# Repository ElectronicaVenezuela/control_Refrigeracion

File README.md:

# Módulo Control De Refrigeracion Comercial

Tesis para obtar al titulo de ingeniero de la Universidad Nacional Experimental del Táchira (UNET).

## Descripcion

Es un control de refrigeracion comercial con control de ciclos y deshielo, asi como tambien alertas contra posibles anomalias en el sistema de refrigeracion.

## Uso:

 - El hartware fue esta siendo desarrollado en [kicad version Nocturna](http://kicad-pcb.org/download/ubuntu/) para Ubuntu.

 - Las librerias usadas de componentes estan en: 
    -[Symbols](https://github.com/picli3/kicad-symbols.git)
    -[FootPrints](https://github.com/picli3/kicad-footprints.git)
    -[Packages3D](https://github.com/picli3/kicad-packages3D.git)
Se deben clonar y asociarse con el proyecto.

## Autor:

Maykol Rey Maykolrey@gmail.com

## Tutor:

Dr. Cesar contreras.

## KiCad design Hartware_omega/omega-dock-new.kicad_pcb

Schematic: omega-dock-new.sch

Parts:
BT1: 3V; BatteryHolder_Keystone_3000_1x12mm
C1: 22uF; CP_Elec_5x5.3
D1, D2, D3, D4, D6, D7: LED; LED_0603_1608Metric_Castellated
D5: Bridge; MBS -1
J1: SI; HE_XDF1B_1x03_P2.50mm_Horizontal
J2: Termistor; JST_XH_S04B-XH-A-1_1x04_P2.50mm_Horizontal
R1, R2, R3: 100; R_0805_2012Metric_Pad1.15x1.50mm_HandSolder
R4, R5: 2.2K; R_0805_2012Metric_Pad1.15x1.50mm_HandSolder
R6, R7: 10K; R_0805_2012Metric_Pad1.15x1.50mm_HandSolder
R8, R22, R24: 100; R_0805_2012Metric_Pad1.29x1.40mm_HandSolder
R19, R20: 604K; R_0805_2012Metric_Pad1.29x1.40mm_HandSolder
R21: 10k; R_0805_2012Metric_Pad1.29x1.40mm_HandSolder
R23: 10K; R_0805_2012Metric_Pad1.29x1.40mm_HandSolder
SW1: RST; Panasonic_EVQPUL_EVQPUC
U2: OMEGA_2
U11: TLA2024IRUGT; PQFP-N10
U12: DS1307Z+; SOIC-8_3.9x4.9mm_P1.27mm
Y1: 32.768KHZ; Crystal_AT310_D3.0mm_L10.0mm_Horizontal

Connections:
+3V3: R4.1, R5.1, R6.1, R7.1, SW1.1, U2.31, U11.8; also elsewhere on the board
+5V: J1.1, U12.8; also elsewhere on the board
+BATT: BT1.1, U12.3
/GPIO: R24.1, U2.19; also elsewhere on the board
/I_TEST: J1.2, U11.7
/OutTriac/Compresor: D3.2, U2.5; also elsewhere on the board
/OutTriac/Resistencia: D1.2, U2.7; also elsewhere on the board
/OutTriac/Ventilador: D2.2, U2.6; also elsewhere on the board
/SCL: R4.2, U2.18, U11.10, U12.6
/SDA: R5.2, U2.17, U11.9, U12.5
/V_TEST: C1.1, R20.2, R21.1, U11.6; also elsewhere on the board
/error: R22.1, U2.2
/red: R8.1, U2.20
GND: BT1.2, C1.2, D4.1, D5.4, D6.1, D7.1, J1.3, J2.2, J2.4, R1.2, R2.2, R3.2, R21.2, R23.2, U2.1, U2.32, U11.1, U11.3, U12.4; also elsewhere on the board
Nac: D5.2; also elsewhere on the board
unnamed: D1.1, R1.1
unnamed: D2.1, R2.1
unnamed: D3.1, R3.1
unnamed: D4.2, R8.2
unnamed: D5.3, R19.1
unnamed: D6.2, R22.2
unnamed: D7.2, R24.2
unnamed: J2.1, R7.2, U11.4
unnamed: J2.3, R6.2, U11.5
unnamed: R19.2, R20.1
unnamed: R23.1, SW1.2, U2.26
unnamed: U12.1, Y1.1
unnamed: U12.2, Y1.2
VacF: D5.1; also elsewhere on the board

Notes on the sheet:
Omega dock\ new
August 7, 2017
1.0
https://github.com/5N44P/omega-dock-new
address->0x48

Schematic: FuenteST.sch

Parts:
C5, C6: 4,7uF; CP_Radial_D8.0mm_P3.50mm
C7: 10uF; CP_Elec_4x5.3
C8: 1nF; C_0805_2012Metric_Pad1.15x1.50mm_HandSolder
C9: 100uF; CP_Elec_4x5.3
C10: 270uF; CP_Elec_6.3x7.7
C11: 68uF; CP_Elec_6.3x7.7
C12: 100nF; C_1206_3216Metric_Pad1.24x1.80mm_HandSolder
F1: 1A; FC-211-22_M
L2: SDR0503-472JL; SDR0503-XXX
L3: 74479776247; L_0805_2012Metric_Pad1.15x1.50mm_HandSolder
RV1: B72214S0351K101; C_Disc_D4.3mm_W1.9mm_P5.00mm
U3: AP111733; SOT-223
U4: PBO-3-S5

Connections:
+3V3: C9.1, U3.2 (VO), U3.4 (VO); also elsewhere on the board
+5V: C7.1, C11.1, C12.1, L3.2, U3.3 (VI); also elsewhere on the board
/FuenteST/VO: C10.1, L3.1, U4.12
GND: C7.2, C8.2, C9.2, C10.2, C11.2, C12.2, U3.1 (GND), U4.10; also elsewhere on the board
Nac: RV1.2, U4.1; also elsewhere on the board
unnamed: C5.1, C6.1, U4.5
unnamed: C5.2, C6.2, C8.1, U4.7
unnamed: L2.2, U4.3
Vac: F1.2; also elsewhere on the board
VacF: F1.1, L2.1, RV1.1; also elsewhere on the board

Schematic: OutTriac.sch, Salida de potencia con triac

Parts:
C13, C14, C15: 1nF; C_Rect_L13.0mm_W4.0mm_P10.00mm_FKS3_FKP3_MKS4
P1: POWER I/O; WE-3221 - 3.50MM
R10, R11, R12, R13, R14, R15: 330; R_0805_2012Metric_Pad1.15x1.50mm_HandSolder
R16, R18: 33; R_Axial_DIN0207_L6.3mm_D2.5mm_P10.16mm_Horizontal
R17: 100; R_Axial_DIN0207_L6.3mm_D2.5mm_P10.16mm_Horizontal
U5, U6, U7: MOC3063S-TA1; MOC306X
U8, U9, U10: Z0103MN 5AA4; SOT-223-Z01

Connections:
/OutTriac/Compresor: U7.1; also elsewhere on the board
/OutTriac/Resistencia: U6.1; also elsewhere on the board
/OutTriac/Ventilador: U5.1; also elsewhere on the board
CO: P1.4, R15.1, R18.1, U10.2
GND: R10.2, R11.2, R12.2; also elsewhere on the board
Nac: C13.2, C14.2, C15.2, P1.1, U8.1, U9.1, U10.1; also elsewhere on the board
unnamed: C13.1, R16.2
unnamed: C14.1, R17.2
unnamed: C15.1, R18.2
unnamed: R10.1, U5.2
unnamed: R11.1, U6.2
unnamed: R12.1, U7.2
unnamed: R13.2, U5.6
unnamed: R14.2, U6.6
unnamed: R15.2, U7.6
unnamed: U5.4, U8.3
unnamed: U6.4, U9.3
unnamed: U7.4, U10.3
RE: P1.3, R14.1, R17.1, U9.2
VE: P1.2, R13.1, R16.1, U8.2
Vac: P1.5; also elsewhere on the board

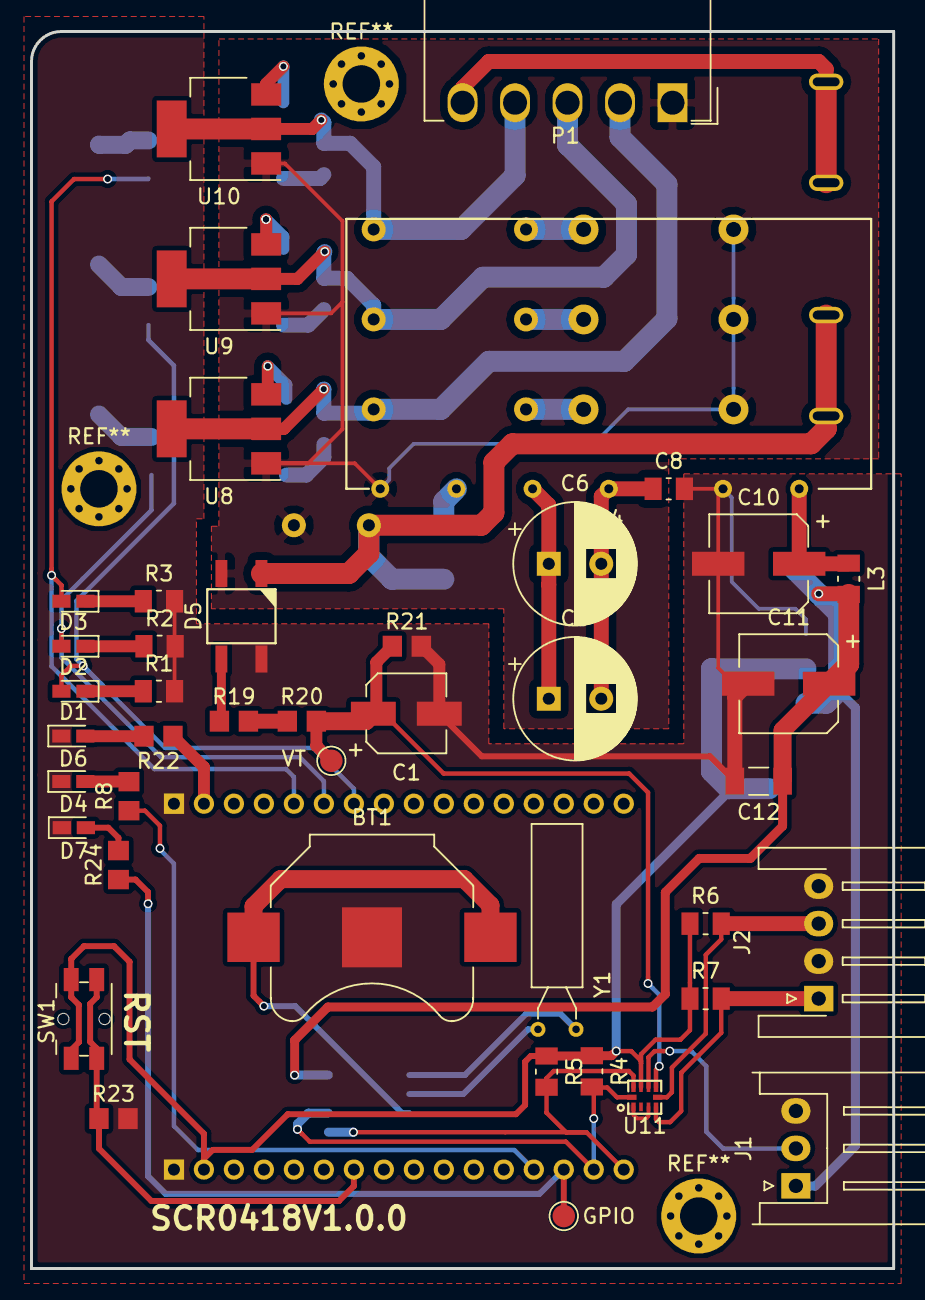
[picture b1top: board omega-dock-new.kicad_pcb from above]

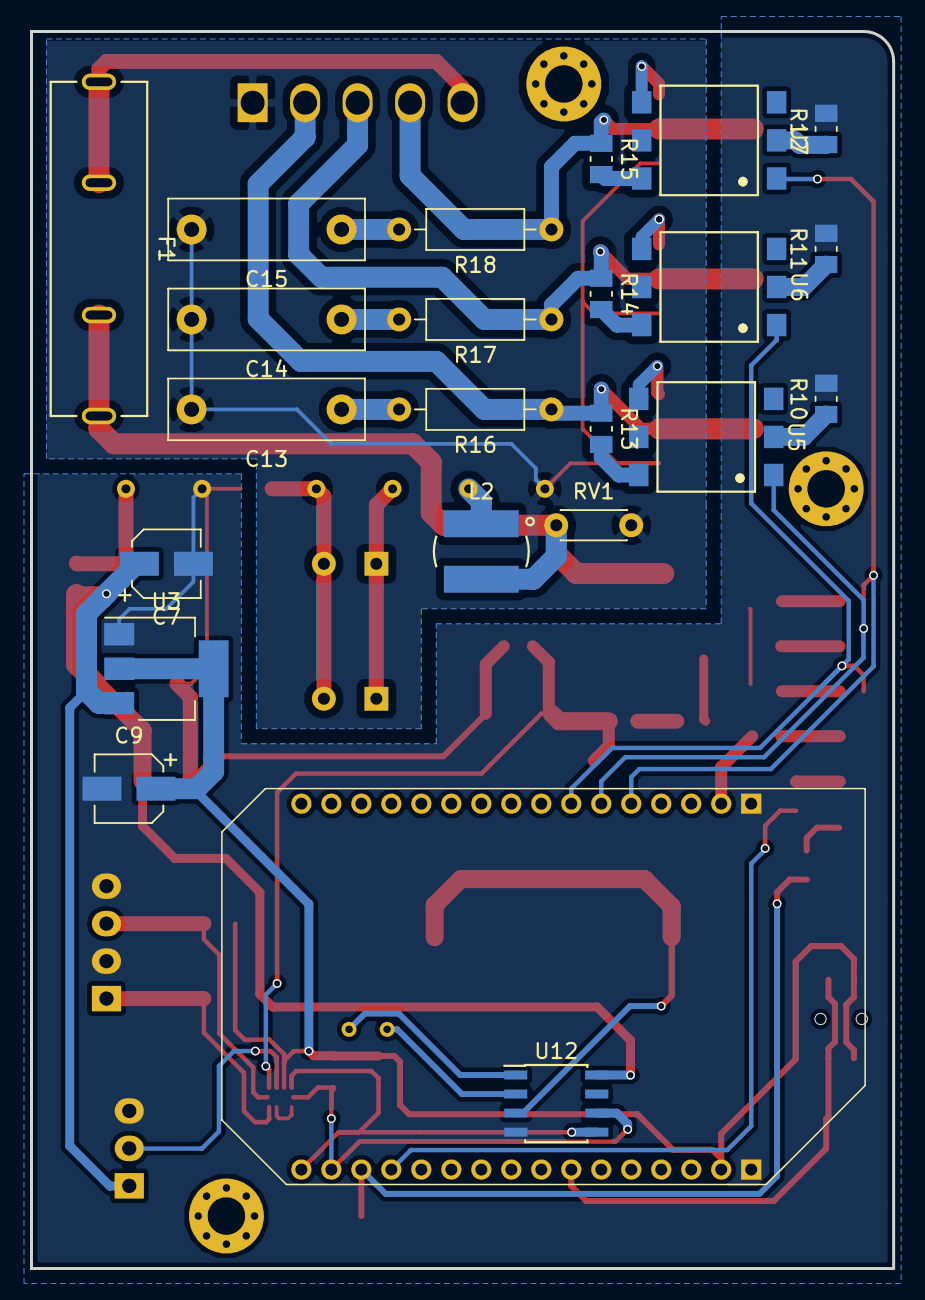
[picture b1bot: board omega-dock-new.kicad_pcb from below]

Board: 2 copper layers, 57.5 x 82.5 mm, 65 parts (23 on the bottom side), 49 nets.

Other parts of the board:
GPIO: TestPoint_Pad_D1.5mm
VT: TestPoint_Pad_D1.5mm

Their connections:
/GPIO: GPIO.1; also elsewhere on the board
/V_TEST: VT.1; also elsewhere on the board

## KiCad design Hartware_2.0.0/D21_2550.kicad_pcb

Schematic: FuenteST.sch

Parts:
C1, C11: 4,7uF; CP_Radial_D8.0mm_P3.50mm
C8: 1nF; C_0805_2012Metric_Pad1.15x1.50mm_HandSolder
C9: 270uF; CP_Elec_6.3x7.7
C10: 68uF; CP_Elec_6.3x7.7
C12: 100nF; C_1206_3216Metric_Pad1.24x1.80mm_HandSolder
L1: SDR0503-472JL; SDR0503-XXX
L2: 74479776247; L_0805_2012Metric_Pad1.15x1.50mm_HandSolder
R1: 300k; R_1206_3216Metric_Pad1.24x1.80mm_HandSolder
RV1: B72214S0351K101; C_Disc_D4.3mm_W1.9mm_P5.00mm
U8: PBO-3-S5

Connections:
/Fuente/VO: C9.1, L2.1, U8.12
GND: C8.2, C9.2, C10.2, C12.2, U8.10; also elsewhere on the board
Nac: RV1.2, U8.1; also elsewhere on the board
unnamed: C1.1, C11.1, U8.5
unnamed: C1.2, C8.1, C11.2, U8.7
unnamed: L1.1, R1.1
unnamed: L1.2, U8.3
VDD: C10.1, C12.1, L2.2; also elsewhere on the board
Vac: R1.2, RV1.1; also elsewhere on the board

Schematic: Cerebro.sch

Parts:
C2, C3: 33pf; C_0805_2012Metric_Pad1.15x1.50mm_HandSolder
D8, D9, D10: LED; LED_0603_1608Metric_Pad0.67x1.00mm_HandSolder
JP1: pgm; PinHeader_1x02_P2.54mm_Vertical
P4: ISCP; PinHeader_1x05_P2.54mm_Vertical
R2: 10k; R_0805_2012Metric_Pad1.15x1.50mm_HandSolder
R24, R25, R26: 220; R_0805_2012Metric_Pad1.15x1.50mm_HandSolder
U1: PIC18F2550-ISO; SOIC-28W_7.5x17.9mm_P1.27mm
Y1: 20MHZ; Crystal_SMD_ABLS_HC49-SD

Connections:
/Cerebro/7 SEGMENTOS/A: U1.21 (RB0/AN12/INT0/FLT0/SDI/SDA); also elsewhere on the board
/Cerebro/7 SEGMENTOS/B: U1.22 (RB1/AN10/INT1/SCK/SCL); also elsewhere on the board
/Cerebro/7 SEGMENTOS/C: U1.23 (RB2/AN8/INT2/VMO); also elsewhere on the board
/Cerebro/7 SEGMENTOS/D: U1.24 (RB3/AN9/CCP2/VPO); also elsewhere on the board
/Cerebro/7 SEGMENTOS/E: U1.25 (RB4/AN11/KBI0); also elsewhere on the board
/Cerebro/7 SEGMENTOS/E1: U1.11 (T1OSO/T13CKI/RC0); also elsewhere on the board
/Cerebro/7 SEGMENTOS/E2: U1.12 (~UOE~/CCP2/T1OSI/RC1); also elsewhere on the board
/Cerebro/7 SEGMENTOS/E3: U1.13 (CCP1/RC2); also elsewhere on the board
/Cerebro/7 SEGMENTOS/F: U1.26 (RB5/KBI1/PGM); also elsewhere on the board
/Cerebro/Acond NTC/T_A: U1.3 (RA1/AN1); also elsewhere on the board
/Cerebro/Acond NTC/T_R: U1.2 (RA0/AN0); also elsewhere on the board
/Cerebro/Botones/+: U1.6 (RA4/T0CKI/C1OUT/RCV); also elsewhere on the board
/Cerebro/Botones/-: U1.7 (RA5/AN4/~SS~/HLVDIN/C2OUT); also elsewhere on the board
/Cerebro/Botones/P: U1.4 (RA2/AN2/Vref-/CVref); also elsewhere on the board
/Cerebro/Botones/S: U1.5 (RA3/AN3/Vref+); also elsewhere on the board
/Cerebro/Salida de potencia/Compresor: R24.1, U1.16 (VP/D+/RC5); also elsewhere on the board
/Cerebro/Salida de potencia/Resistencia: R26.1, U1.18 (SDO/RX/DT/RC7); also elsewhere on the board
/Cerebro/Salida de potencia/Ventilador: R25.1, U1.17 (TX/CK/RC6); also elsewhere on the board
GND: C2.2, C3.2, D8.1, D9.1, D10.1, P4.3, U1.8 (VSS), U1.19 (VSS); also elsewhere on the board
K1: C2.1, U1.10 (RA6/OSC2/CLKO), Y1.1
K2: C3.1, U1.9 (OSC1/CLKI), Y1.2
unnamed: D8.2, R24.2
unnamed: D9.2, R25.2
unnamed: D10.2, R26.2
PGC: P4.1, U1.27 (RB6/KBI2/PGC); also elsewhere on the board
PGD: P4.2, U1.28 (RB7/KBI3/PGD); also elsewhere on the board
VDD: JP1.1, R2.1; also elsewhere on the board
VDDP: JP1.2, P4.4, U1.20 (VDD); also elsewhere on the board
VPP: P4.5, R2.2, U1.1 (Vpp/~MCLR~/RE3)

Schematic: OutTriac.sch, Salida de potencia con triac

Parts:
C4, C5, C6: 1nF; C_Rect_L13.0mm_W4.0mm_P10.00mm_FKS3_FKP3_MKS4
P1: POWER I/O; TerminalBlock_bornier-5_P5.08mm
R3, R4, R5, R6, R7, R8: 330; R_0805_2012Metric_Pad1.15x1.50mm_HandSolder
R9, R10: 33; R_Axial_DIN0207_L6.3mm_D2.5mm_P10.16mm_Horizontal
R11: 100; R_Axial_DIN0207_L6.3mm_D2.5mm_P10.16mm_Horizontal
U2, U3, U4: MOC3063S-TA1; MOC306X
U5, U6, U7: Z0103MN 5AA4; SOT-223-Z01

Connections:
/Cerebro/Salida de potencia/Compresor: U2.1; also elsewhere on the board
/Cerebro/Salida de potencia/Resistencia: U4.1; also elsewhere on the board
/Cerebro/Salida de potencia/Ventilador: U3.1; also elsewhere on the board
CO: P1.2, R6.1, R9.1, U5.2
GND: R3.2, R4.2, R5.2; also elsewhere on the board
Nac: C4.2, C5.2, C6.2, P1.5, U5.1, U6.1, U7.1; also elsewhere on the board
unnamed: C4.1, R9.2
unnamed: C5.1, R10.2
unnamed: C6.1, R11.2
unnamed: R3.1, U2.2
unnamed: R4.1, U3.2
unnamed: R5.1, U4.2
unnamed: R6.2, U2.6
unnamed: R7.2, U3.6
unnamed: R8.2, U4.6
unnamed: U2.4, U5.3
unnamed: U3.4, U6.3
unnamed: U4.4, U7.3
RE: P1.4, R8.1, R11.1, U7.2
VE: P1.3, R7.1, R10.1, U6.2
Vac: P1.1; also elsewhere on the board

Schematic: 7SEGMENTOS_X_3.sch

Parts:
D11: LTC-4724JR
Q1, Q2, Q3: FZT493TA; SOT-223
R12, R13, R14: 2.7k; R_0805_2012Metric_Pad1.15x1.50mm_HandSolder
R15, R16, R17: 22; R_2512_6332Metric_Pad1.34x3.40mm_HandSolder

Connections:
/Cerebro/7 SEGMENTOS/A: D11.12; also elsewhere on the board
/Cerebro/7 SEGMENTOS/B: D11.11; also elsewhere on the board
/Cerebro/7 SEGMENTOS/C: D11.3; also elsewhere on the board
/Cerebro/7 SEGMENTOS/D: D11.4; also elsewhere on the board
/Cerebro/7 SEGMENTOS/E: D11.2; also elsewhere on the board
/Cerebro/7 SEGMENTOS/E1: R12.2; also elsewhere on the board
/Cerebro/7 SEGMENTOS/E2: R13.2; also elsewhere on the board
/Cerebro/7 SEGMENTOS/E3: R14.2; also elsewhere on the board
/Cerebro/7 SEGMENTOS/F: D11.15; also elsewhere on the board
GND: Q1.3, Q2.3, Q3.3; also elsewhere on the board
unnamed: D11.1, R15.2
unnamed: D11.5, R16.2
unnamed: D11.7, R17.2
unnamed: Q1.1, R15.1
unnamed: Q1.2, R12.1
unnamed: Q2.1, R16.1
unnamed: Q2.2, R13.1
unnamed: Q3.1, R17.1
unnamed: Q3.2, R14.1
PGC: D11.8; also elsewhere on the board
PGD: D11.6; also elsewhere on the board

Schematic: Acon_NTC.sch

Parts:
J1: THR; JST_XH_S04B-XH-A-1_1x04_P2.50mm_Horizontal
R18, R19: 20k; R_0805_2012Metric_Pad1.15x1.50mm_HandSolder

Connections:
/Cerebro/Acond NTC/T_A: J1.4, R18.2; also elsewhere on the board
/Cerebro/Acond NTC/T_R: J1.2, R19.2; also elsewhere on the board
GND: J1.1, J1.3; also elsewhere on the board
VDD: R18.1, R19.1; also elsewhere on the board

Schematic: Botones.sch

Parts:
R20, R21, R22, R23: 10k; R_0805_2012Metric_Pad1.15x1.50mm_HandSolder
SW1, SW2, SW3, SW4: TL3301AF160QG

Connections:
/Cerebro/Botones/+: R20.2, SW1.2; also elsewhere on the board
/Cerebro/Botones/-: R21.2, SW2.2; also elsewhere on the board
/Cerebro/Botones/P: R22.2, SW3.1; also elsewhere on the board
/Cerebro/Botones/S: R23.2, SW4.1; also elsewhere on the board
GND: SW1.1, SW2.1, SW3.2, SW4.2; also elsewhere on the board
VDD: R20.1, R21.1, R22.1, R23.1; also elsewhere on the board

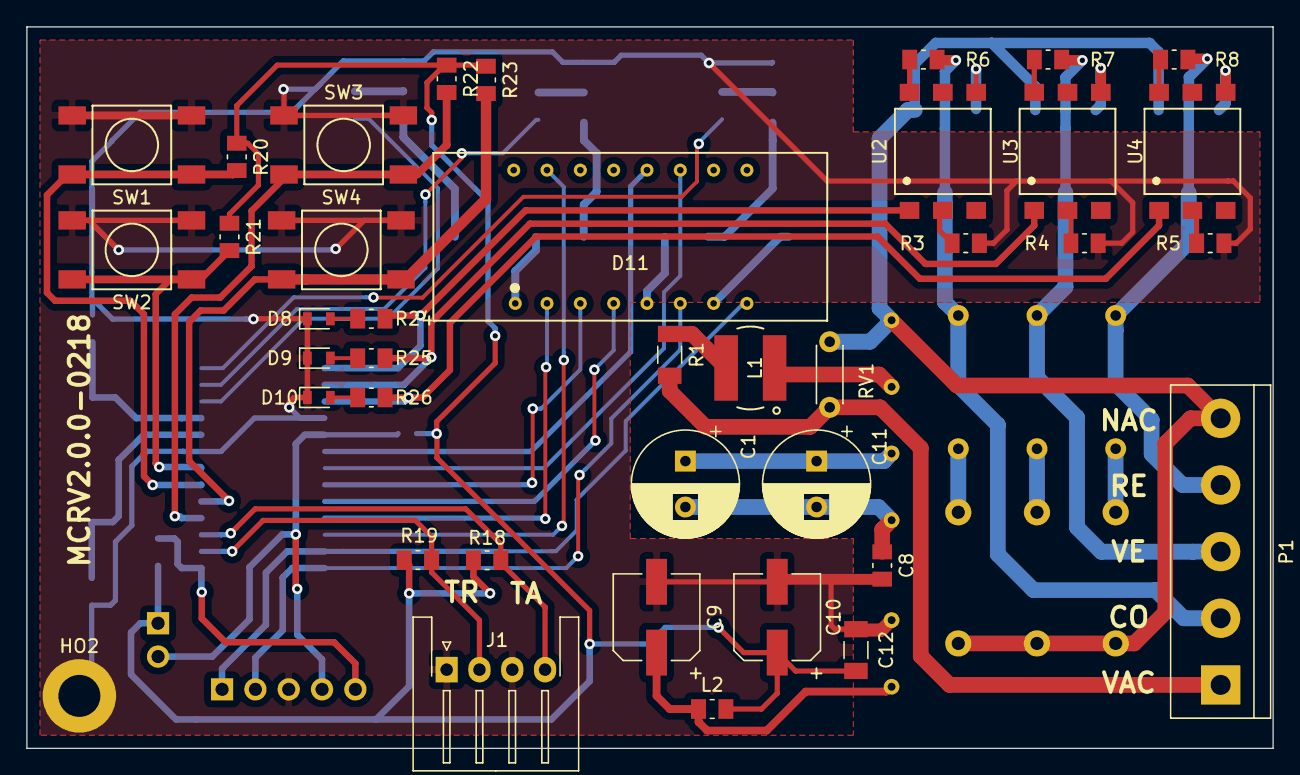
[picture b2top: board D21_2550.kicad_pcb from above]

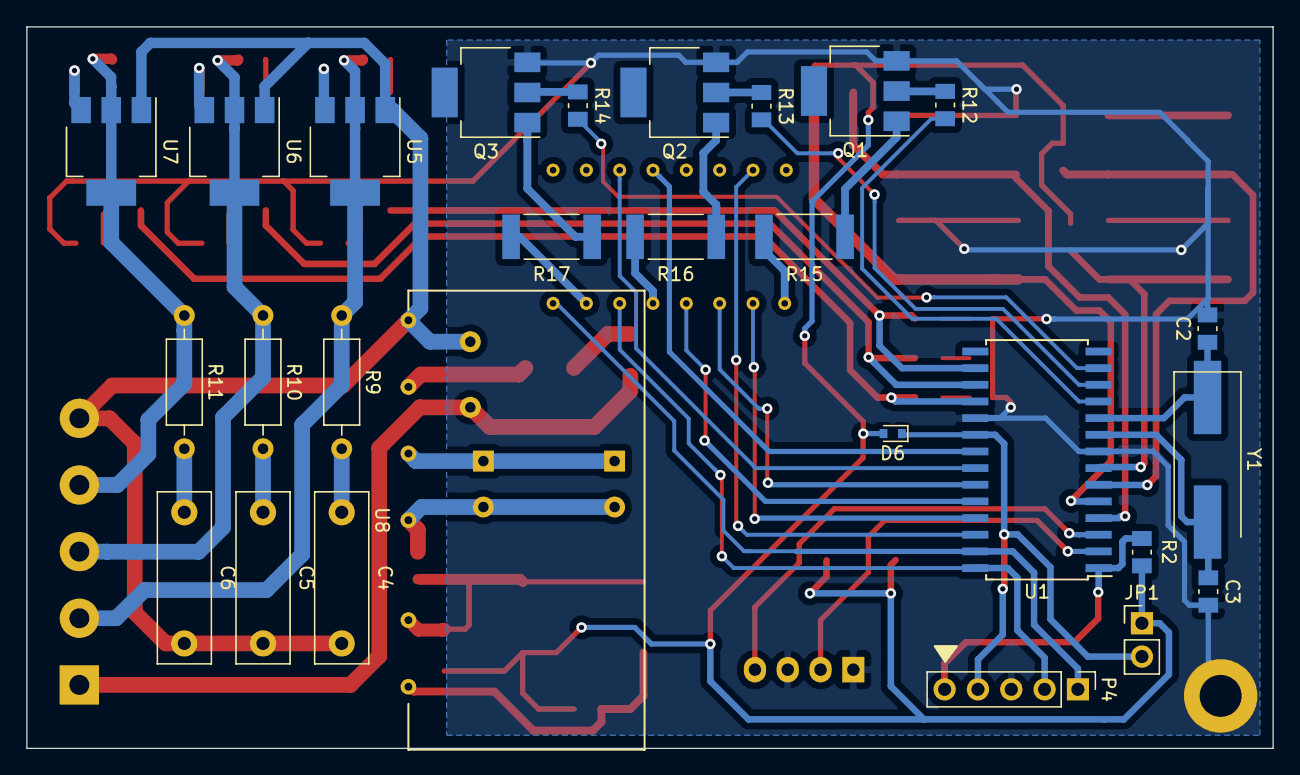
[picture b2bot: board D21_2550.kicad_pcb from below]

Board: 2 copper layers, 95.0 x 55.0 mm, 66 parts (27 on the bottom side), 60 nets.

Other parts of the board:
D6: 1N4148X-TP; D_SOD-523
HO2: MountingHole_3.2mm_M3_DIN965_Pad

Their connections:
GND: HO2.1; also elsewhere on the board
VDD: D6.2; also elsewhere on the board
VDDP: D6.1; also elsewhere on the board

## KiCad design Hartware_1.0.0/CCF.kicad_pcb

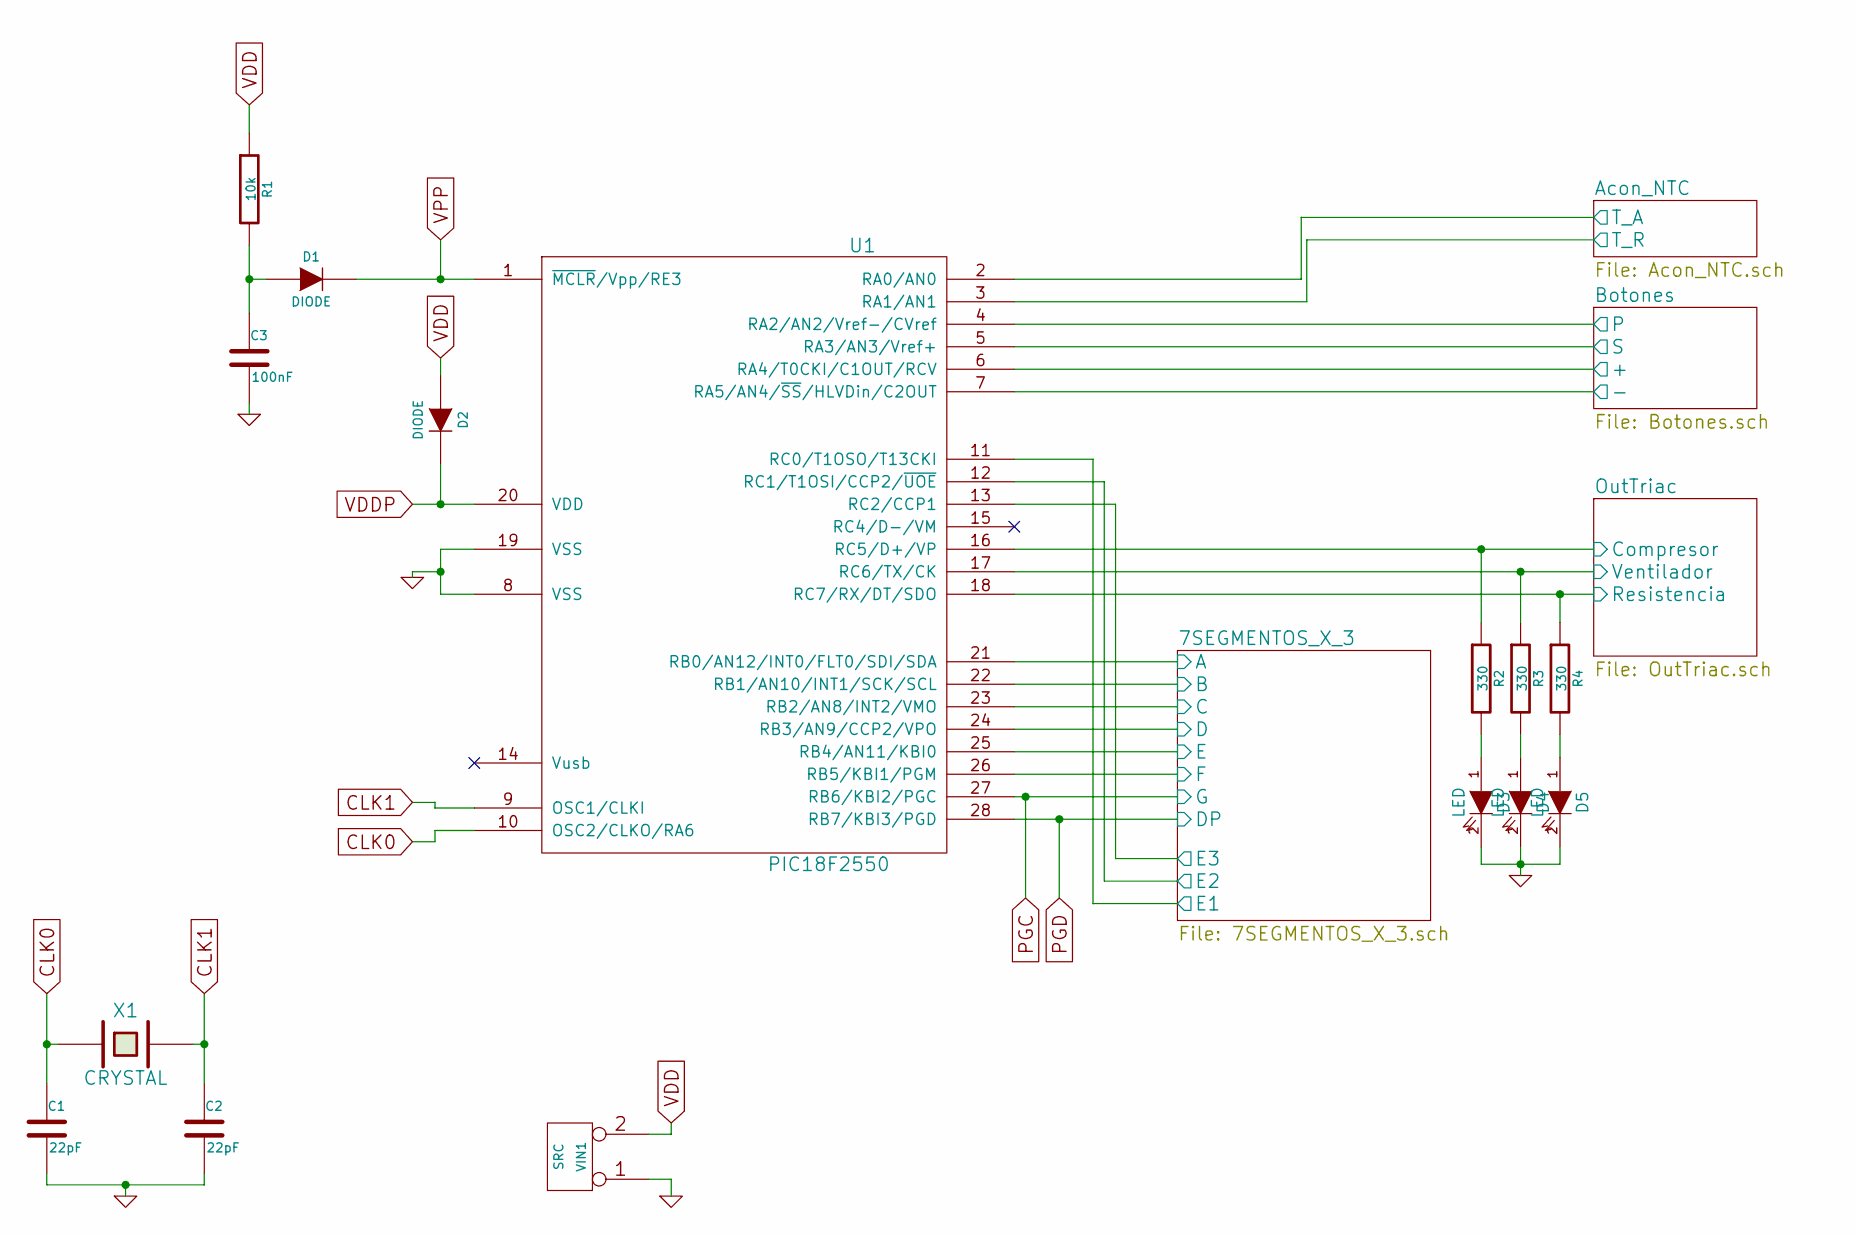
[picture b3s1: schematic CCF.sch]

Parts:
C1, C2: 22pF; C_Disc_D3_P2.5
C3: 100nF; C_Disc_D3_P2.5
D1, D2: DIODE; Diode_DO-35_SOD27_Horizontal_RM10
D3, D4, D5: LED; LED-3MM
R1: 10k; Resistor_Horizontal_RM10mm
R2, R3, R4: 330; Resistor_Horizontal_RM10mm
U1: PIC18F2550; DIP-28_W7.62mm_LongPads
VIN1: SRC; JACK_ALIM
X1: CRYSTAL; HC-49V

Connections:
/7SEGMENTOS_X_3/A: U1.21 (RB0/AN12/INT0/FLT0/SDI/SDA); also elsewhere on the board
/7SEGMENTOS_X_3/B: U1.22 (RB1/AN10/INT1/SCK/SCL); also elsewhere on the board
/7SEGMENTOS_X_3/C: U1.23 (RB2/AN8/INT2/VMO); also elsewhere on the board
/7SEGMENTOS_X_3/D: U1.24 (RB3/AN9/CCP2/VPO); also elsewhere on the board
/7SEGMENTOS_X_3/E: U1.25 (RB4/AN11/KBI0); also elsewhere on the board
/7SEGMENTOS_X_3/E1: U1.11 (RC0/T1OSO/T13CKI); also elsewhere on the board
/7SEGMENTOS_X_3/E2: U1.12 (RC1/T1OSI/CCP2/~UOE); also elsewhere on the board
/7SEGMENTOS_X_3/E3: U1.13 (RC2/CCP1); also elsewhere on the board
/7SEGMENTOS_X_3/F: U1.26 (RB5/KBI1/PGM); also elsewhere on the board
/Acon_NTC/T_A: U1.2 (RA0/AN0); also elsewhere on the board
/Acon_NTC/T_R: U1.3 (RA1/AN1); also elsewhere on the board
/Botones/+: U1.6 (RA4/T0CKI/C1OUT/RCV); also elsewhere on the board
/Botones/-: U1.7 (RA5/AN4/~SS~/HLVDin/C2OUT); also elsewhere on the board
/Botones/P: U1.4 (RA2/AN2/Vref-/CVref); also elsewhere on the board
/Botones/S: U1.5 (RA3/AN3/Vref+); also elsewhere on the board
/OutTriac/Compresor: R2.1, U1.16 (RC5/D+/VP); also elsewhere on the board
/OutTriac/Resistencia: R4.1, U1.18 (RC7/RX/DT/SDO); also elsewhere on the board
/OutTriac/Ventilador: R3.1, U1.17 (RC6/TX/CK); also elsewhere on the board
CLK0: C1.1, U1.10 (OSC2/CLKO/RA6), X1.1
CLK1: C2.1, U1.9 (OSC1/CLKI), X1.2
GND: C1.2, C2.2, C3.2, D3.2 (K), D4.2 (K), D5.2 (K), U1.8 (VSS), U1.19 (VSS), VIN1.1; also elsewhere on the board
unnamed: C3.1, D1.1 (A), R1.2
unnamed: D3.1 (A), R2.2
unnamed: D4.1 (A), R3.2
unnamed: D5.1 (A), R4.2
PGC: U1.27 (RB6/KBI2/PGC); also elsewhere on the board
PGD: U1.28 (RB7/KBI3/PGD); also elsewhere on the board
VDD: D2.1 (A), R1.1, VIN1.2 (PM); also elsewhere on the board
VDDP: D2.2 (K), U1.20 (VDD)
VPP: D1.2 (K), U1.1 (~MCLR~/Vpp/RE3)

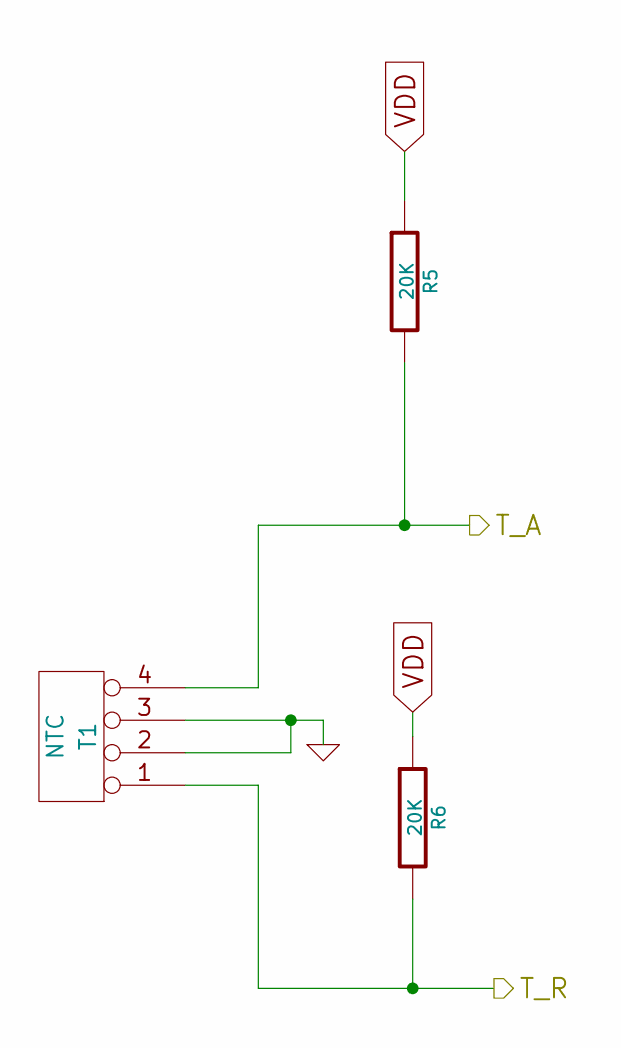
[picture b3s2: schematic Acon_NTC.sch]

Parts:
R5, R6: 20K; Resistor_Horizontal_RM10mm
T1: NTC; Socket_Strip_Straight_1x04

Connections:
/Acon_NTC/T_A: R5.2, T1.4; also elsewhere on the board
/Acon_NTC/T_R: R6.2, T1.1; also elsewhere on the board
GND: T1.2, T1.3; also elsewhere on the board
VDD: R5.1, R6.1; also elsewhere on the board

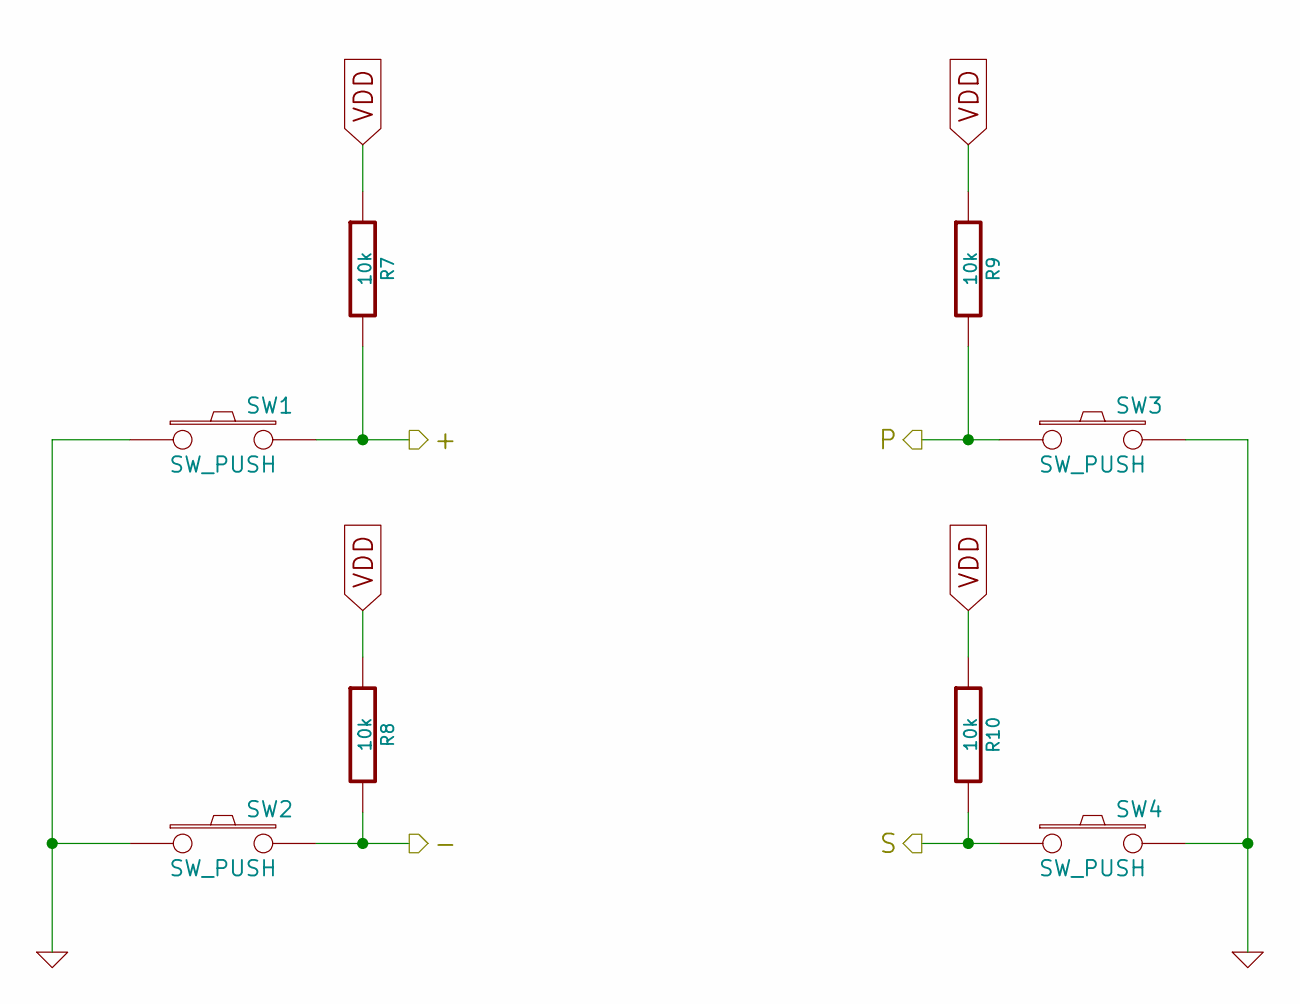
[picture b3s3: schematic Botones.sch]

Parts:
R7, R8, R9, R10: 10k; Resistor_Horizontal_RM10mm
SW1, SW2, SW3, SW4: SW_PUSH; SW_PUSH-12mm

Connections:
/Botones/+: R7.2, SW1.2; also elsewhere on the board
/Botones/-: R8.2, SW2.2; also elsewhere on the board
/Botones/P: R9.2, SW3.1; also elsewhere on the board
/Botones/S: R10.2, SW4.1; also elsewhere on the board
GND: SW1.1, SW2.1, SW3.2, SW4.2; also elsewhere on the board
VDD: R7.1, R8.1, R9.1, R10.1; also elsewhere on the board

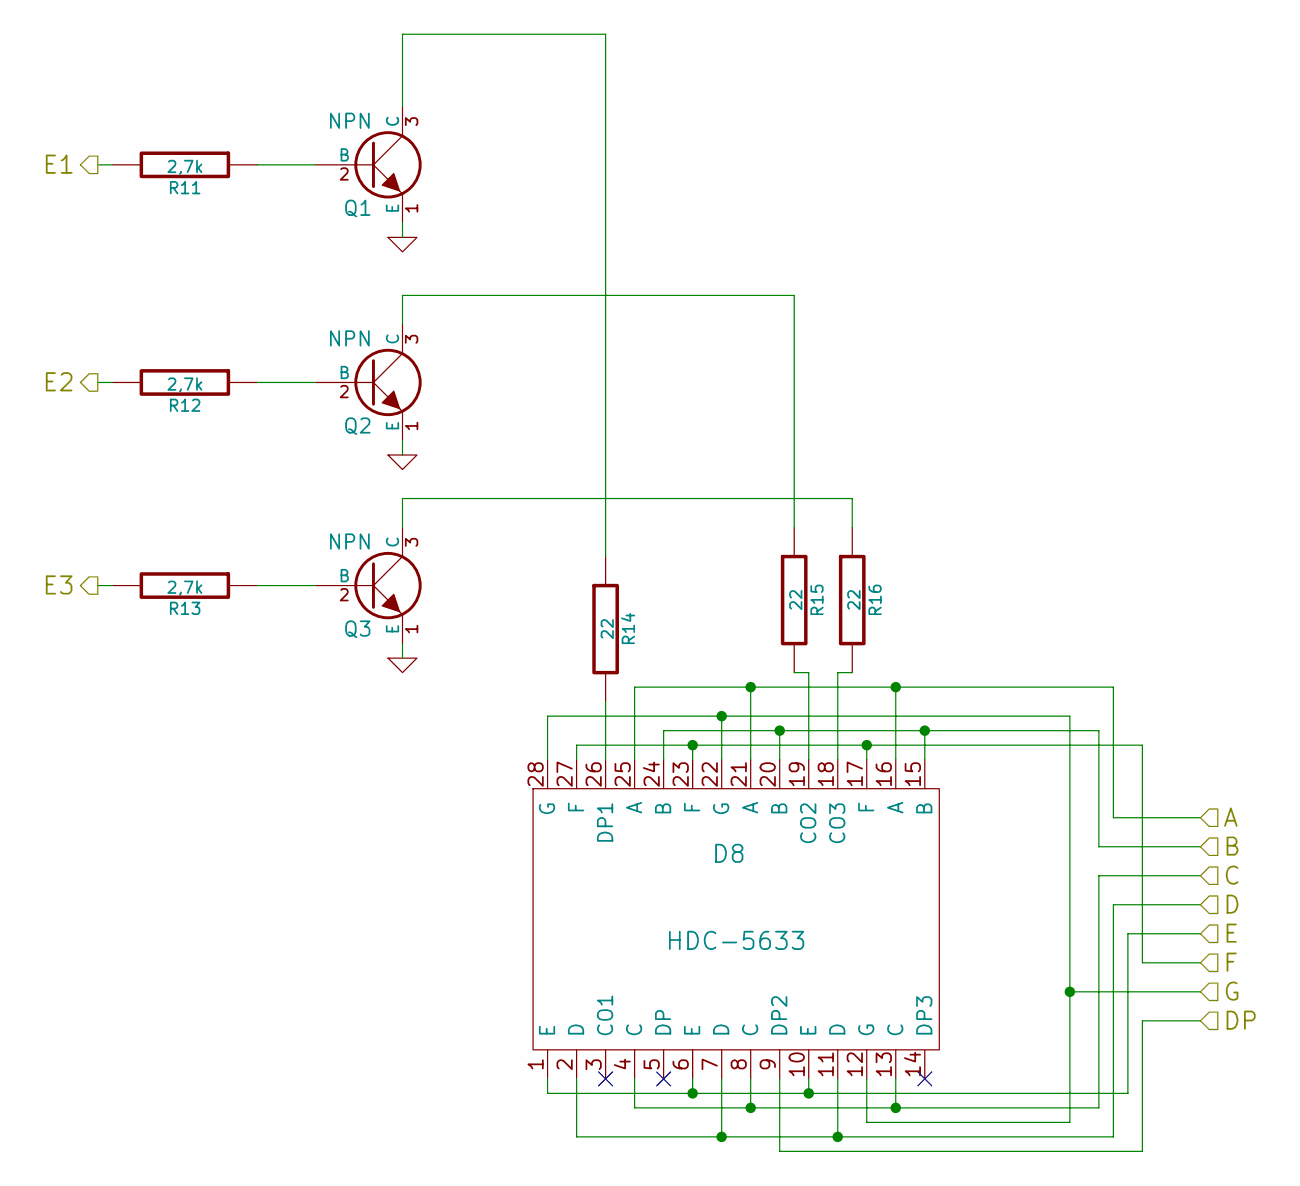
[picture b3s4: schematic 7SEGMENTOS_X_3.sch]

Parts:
D8: HDC-5633; 7seg-HDC-19x37.5mm
Q1, Q2, Q3: NPN; TO-92_Inline_Narrow_Oval
R11, R12, R13: 2,7k; Resistor_Horizontal_RM10mm
R14, R15, R16: 22; Resistor_Horizontal_RM15mm

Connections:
/7SEGMENTOS_X_3/A: D8.16 (A), D8.21 (A), D8.25 (A); also elsewhere on the board
/7SEGMENTOS_X_3/B: D8.15 (B), D8.20 (B), D8.24 (B); also elsewhere on the board
/7SEGMENTOS_X_3/C: D8.4 (C), D8.8 (C), D8.13 (C); also elsewhere on the board
/7SEGMENTOS_X_3/D: D8.2 (D), D8.7 (D), D8.11 (D); also elsewhere on the board
/7SEGMENTOS_X_3/E: D8.1 (E), D8.6 (E), D8.10 (E); also elsewhere on the board
/7SEGMENTOS_X_3/E1: R11.2; also elsewhere on the board
/7SEGMENTOS_X_3/E2: R12.2; also elsewhere on the board
/7SEGMENTOS_X_3/E3: R13.2; also elsewhere on the board
/7SEGMENTOS_X_3/F: D8.17 (F), D8.23 (F), D8.27 (F); also elsewhere on the board
GND: Q1.1 (E), Q2.1 (E), Q3.1 (E); also elsewhere on the board
unnamed: D8.18 (CO3), R16.2
unnamed: D8.19 (CO2), R15.2
unnamed: D8.26 (DP1), R14.2
unnamed: Q1.2 (B), R11.1
unnamed: Q1.3 (C), R14.1
unnamed: Q2.2 (B), R12.1
unnamed: Q2.3 (C), R15.1
unnamed: Q3.2 (B), R13.1
unnamed: Q3.3 (C), R16.1
PGC: D8.12 (G), D8.22 (G), D8.28 (G); also elsewhere on the board
PGD: D8.9 (DP2); also elsewhere on the board

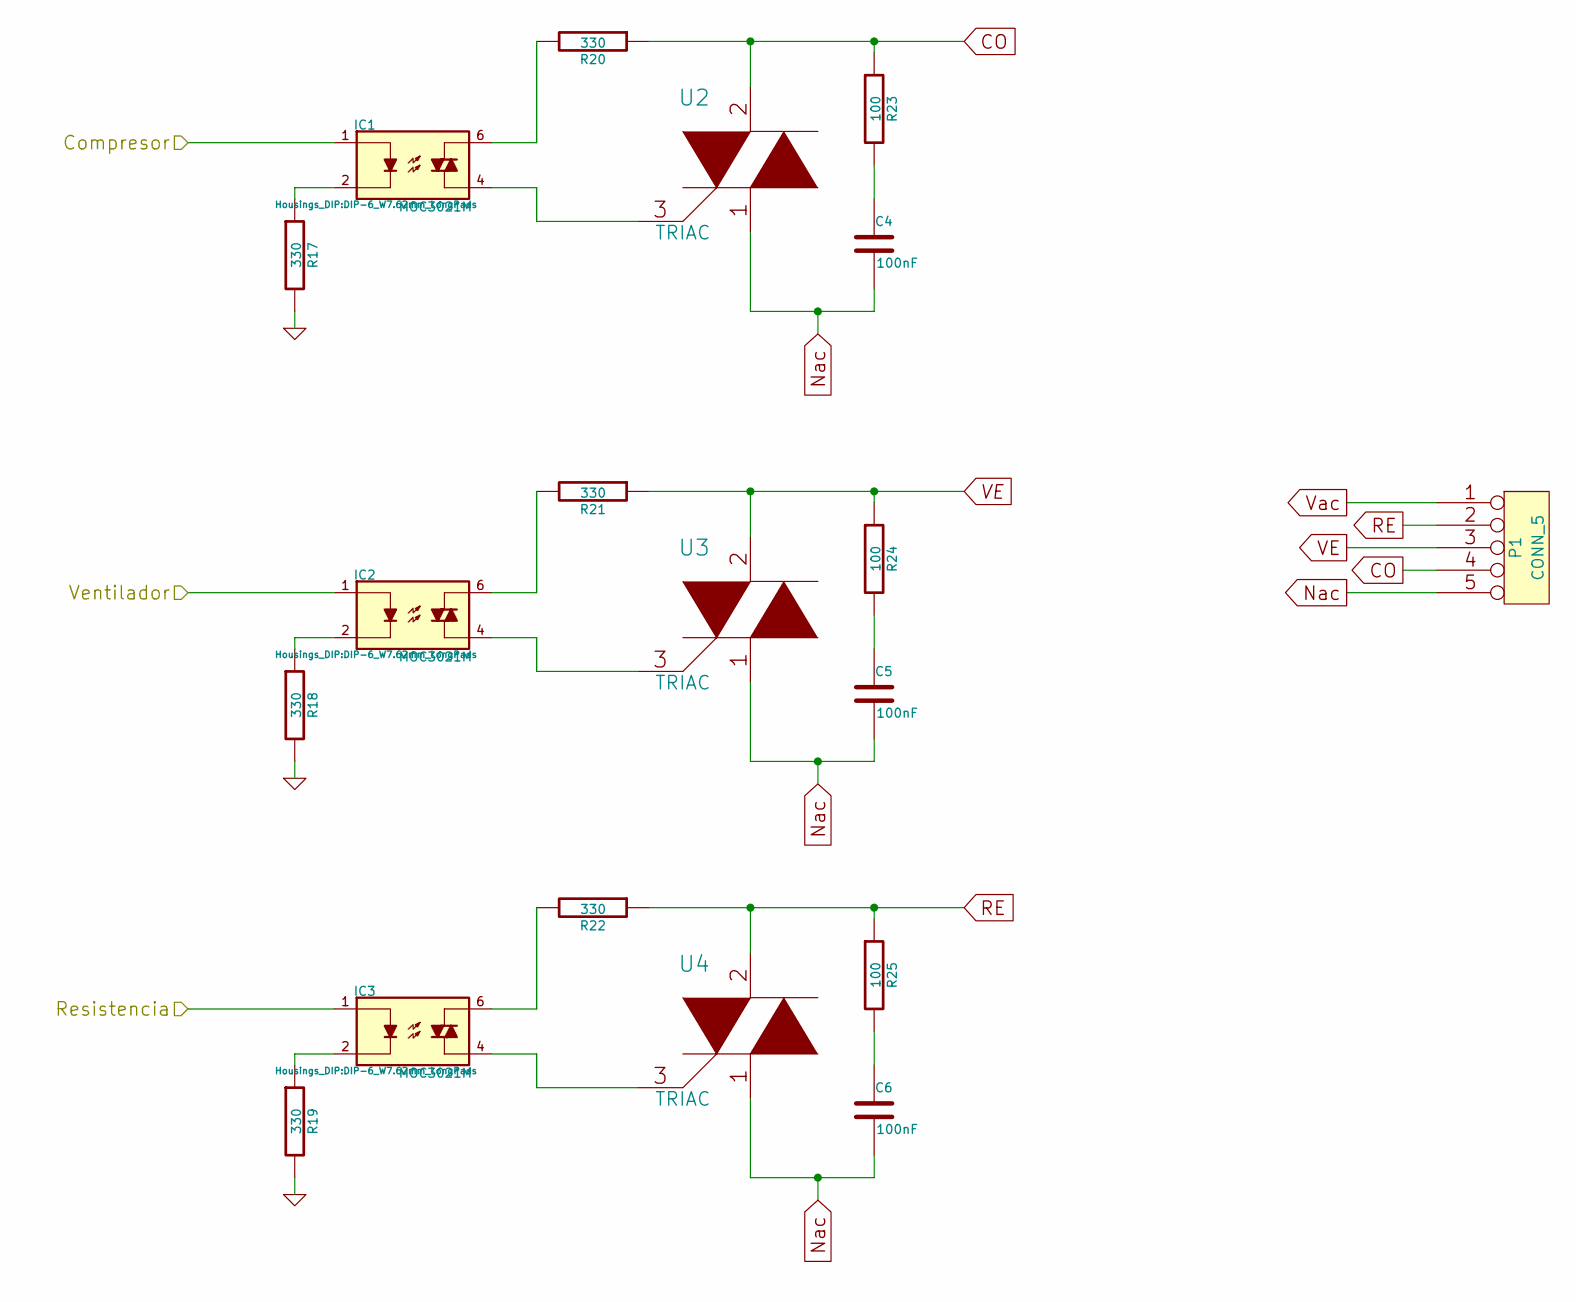
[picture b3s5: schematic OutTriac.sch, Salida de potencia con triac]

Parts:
C4, C5, C6: 100nF; C_Disc_D3_P2.5
IC1, IC2, IC3: MOC3021M; DIP-6_W7.62mm_LongPads
P1: CONN_5; TerminalBlock_Pheonix_MKDS1.5-5pol
R17, R18, R19, R20, R21, R22: 330; Resistor_Horizontal_RM10mm
R23, R24, R25: 100; Resistor_Horizontal_RM10mm
U2, U3, U4: TRIAC; TO-92_Inline_Wide

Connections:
/OutTriac/Compresor: IC1.1; also elsewhere on the board
/OutTriac/Resistencia: IC3.1; also elsewhere on the board
/OutTriac/Ventilador: IC2.1; also elsewhere on the board
CO: P1.4, R20.1, R23.1, U2.2
GND: R17.2, R18.2, R19.2; also elsewhere on the board
Nac: C4.2, C5.2, C6.2, P1.5, U2.1, U3.1, U4.1
unnamed: C4.1, R23.2
unnamed: C5.1, R24.2
unnamed: C6.1, R25.2
unnamed: IC1.2, R17.1
unnamed: IC1.4, U2.3
unnamed: IC1.6, R20.2
unnamed: IC2.2, R18.1
unnamed: IC2.4, U3.3
unnamed: IC2.6, R21.2
unnamed: IC3.2, R19.1
unnamed: IC3.4, U4.3
unnamed: IC3.6, R22.2
RE: P1.2, R22.1, R25.1, U4.2
VE: P1.3, R21.1, R24.1, U3.2
Vac: P1.1
